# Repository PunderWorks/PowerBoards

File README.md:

# Power Boards

Small PCBs for power regulation and distribution.

Each board's electrical design is written in [Stackup](https://github.com/stackup-eda/stackup) KDL, which
is the source of truth for the circuit; there are no KiCad schematics. The layout is done in KiCad
(currently 10), linked to the KDL through a `.stackup_sch` file and synced with the Stackup KiCad plugin.

## Boards

<p align="center">

</p>

| Board | Folder | Purpose | Status |
|---|---|---|---|
| Regulator | [`PCB/regulator/`](PCB/regulator) | A plug-in Pololu D42V55Fx regulator (any output version: 5 V, 12 V, ...) feeding four WAGO 2601 outputs over V+ and GND planes. 9-32 V in, 6 A out (5 A with the 12 V module) | Design done, first-pass layout |
| Distribution | [`PCB/distribution/`](PCB/distribution) | Six interchangeable power terminals in a 3 x 2 grid (any one can be the input) over shared V+ and GND planes, WAGO 2601 lever terminals. 17.5 A total | Initial layout done |
| Distribution, inline | [`PCB/distribution-inline/`](PCB/distribution-inline) | The distribution board with five terminals in a single row (65.5 x 24 mm). 17.5 A total | Initial layout done |

Each board's README has its ratings, a parts list with Mouser, DigiKey and LCSC numbers, assembly
steps and the design decisions behind it. The purchasing BOM for each is in
`PCB/<board>/production/bom/`.

## Repository layout

| Path | Contents |
|---|---|
| [`manifest.kdl`](manifest.kdl) | Stackup version and the parts library, pinned by commit. Shared by every board |
| `PCB/<board>/` | One folder per board: its KiCad project (`<board>.kicad_pro`, `.kicad_pcb`, `.stackup_sch`) and the folders below |
| `PCB/<board>/stackup/` | `board.kdl`, the board's circuit |
| [`PCB/libraries/stackup/`](PCB/libraries/stackup) | `parts.kdl`, the Stackup parts shared by every board |
| `PCB/<board>/diagrams/` | Layout floorplans for circuits with real layout stakes (switching loops, thermal pads, high-current paths) |
| `PCB/<board>/analysis/` | Generated analysis output. Only `manifest.json` is committed |
| `PCB/<board>/assets/` | Board renders used in the READMEs |
| `PCB/<board>/production/` | Fab outputs: `bom/` (the purchasing BOM), `gerbers/`, `jlcpcb/`, `placement/` |
| [`PCB/libraries/`](PCB/libraries) | KiCad footprints (`PowerBoards.pretty`) and 3D models shared by all boards |
| [`PCB/datasheets/`](PCB/datasheets) | Manufacturer datasheets for the parts used, shared by all boards |
| [`scripts/export_production.sh`](scripts/export_production.sh) | Regenerates every board's `production/` files |
| [`scripts/spice/`](scripts/spice) | ngspice simulations of the power, enable and protection circuits |
| [`graphics/`](graphics) | Logos and images |

To add a board, create `PCB/<board>/` with the same subfolders as an existing one and add it to the
table above.

## Working on a board

Run these from the repository root.

```bash
# Check the circuit
stackup check PCB/<board>/stackup/board.kdl

# Export the purchasing BOM
stackup bom PCB/<board>/stackup/board.kdl --locked -o <board>-bom.csv

# Regenerate the fab files (BOM, Gerbers, drills, placement, upload zip) for one board or all of them
scripts/export_production.sh [<board>]
```

After `stackup check` passes, open `PCB/<board>/<board>.kicad_pcb` in KiCad and sync it with the Stackup
plugin.

## Contributing

All changes go through pull requests; nothing is pushed directly to `main`. History is kept linear, so
PRs land by rebase.

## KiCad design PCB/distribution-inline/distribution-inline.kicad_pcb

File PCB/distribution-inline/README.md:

# Inline Distribution Board

Five identical 2-pole terminals in a single row share a V+ plane (`VPWR`, top copper) and a ground
plane (`GND`, bottom copper). Any terminal can be the input; the other four are outputs. There are no
active or passive components.

This is the [distribution board](../distribution/README.md) laid out in one row instead of a 3 x 2 grid,
for where a long, narrow board fits better. The terminal, ratings and design decisions are the same;
only the layout differs, and that is described here.

## Features

- **One in, four out, any way round.** Every terminal is the same, so any one can be the input.
- **17.5 A total** through solid copper planes on both layers, with 16 AWG wire.
- **Tool-free wiring.** WAGO 2601 lever terminals take 26-16 AWG wire; strip 8-9 mm and push it in.
- **Long and narrow.** 65.5 x 24 mm, with every wire leaving from the same edge.
- **Safe to mount with metal hardware.** Four M3 holes with copper kept clear of each.
- **Five parts, all through-hole.**

## Ratings

| | |
|---|---|
| Current | **17.5 A total** through whichever terminal is the input, with 16 AWG wire (IEC/EN 60664-1 rating of the terminals). **10 A** if you need the UL/CSA rating. |
| Wire | 26-16 AWG solid, 24-16 AWG fine-stranded. Strip 8-9 mm. |
| Voltage | DC power distribution, far below the terminals' 160 V IEC / 300 V UL rating. |
| Polarity | `+` and `-` are printed behind every terminal. Any terminal can be the input. |
| Mounting | Four M3 holes. Screws and standoffs may be metal: copper is kept clear of every hole. |

The input terminal carries the sum of every output's current, so the 17.5 A limit applies to the total,
not to each output. See the [distribution board README](../distribution/README.md#terminal-wago-2601-1102)
for the terminal's datasheet figures.

The electrical design is in [Stackup KDL](stackup/board.kdl), using the shared
[parts file](../libraries/stackup/parts.kdl). The KiCad PCB (`distribution-inline.kicad_pcb`) is linked
to it through `distribution-inline.stackup_sch`; sync it with the Stackup KiCad plugin. Run
`stackup check PCB/distribution-inline/stackup/board.kdl --locked` from the repository root before
syncing.

## What to buy

The purchasing BOM is [`production/bom/distribution-inline-bom.csv`](production/bom/distribution-inline-bom.csv), exported from
the Stackup design (`stackup bom PCB/distribution-inline/stackup/board.kdl --locked`).

| Qty | Ref | Part | Manufacturer / MPN | Mouser | DigiKey | LCSC |
|---|---|---|---|---|---|---|
| 5 | J1-J5 | Lever terminal, 2-pole, 3.5 mm, horizontal entry | WAGO 2601-1102 | 1089-2601-1102 | 2946-2601-1102-ND | C7509568 |
| 4 | — | M3 screws and standoffs to mount the board (not on the BOM) | Any; metal is fine, copper is kept clear of the holes | | | |

The 2601-3102 is the vertical, top-entry version of the same block; it is not a substitute.

## Ordering

Fab files are in [`production/`](production/), regenerated with `scripts/export_production.sh distribution-inline`
from the repository root:

| File | Contents |
|---|---|
| [`production/jlcpcb/distribution-inline-gerbers.zip`](production/jlcpcb/distribution-inline-gerbers.zip) | Everything a fab needs to make the bare board: upload this |
| [`production/gerbers/`](production/gerbers/) | The same files unzipped: Gerbers (X2, Protel extensions), PTH and NPTH Excellon drills, drill maps, job file |
| [`production/bom/distribution-inline-bom.csv`](production/bom/distribution-inline-bom.csv) | Purchasing BOM with Mouser, DigiKey and LCSC numbers |
| [`production/placement/distribution-inline-pos.csv`](production/placement/distribution-inline-pos.csv) | Placement file (mm), for an assembler |

Board options: **65.5 x 24 mm, 2 layers, 1.6 mm FR-4, 1 oz copper, blue solder mask, white silkscreen**,
any surface finish (HASL lead-free is fine). Every feature is far above standard fab minimums. The five terminals are through-hole and quick to hand-solder; JLCPCB can also assemble them (LCSC C7509568).

## Assembly

1. Fit the 5 terminals with their wire entries at the board edge and solder both pins of each pole.
   The pins carry the full current, so make them full, shiny fillets.
2. Check continuity between all 5 `+` pins and between all 5 `-` pins, and that `+` and `-` are
   not shorted.
3. Wire the supply to any one terminal and the loads to the others, keeping the total within the rating.

## Hardware overview

| Ref | Function | Part |
|---|---|---|
| J1-J5 | Power terminal, input or output | WAGO 2601-1102 |

Every terminal has pin 1 (square pad, `+` on the silkscreen) on `VPWR` and pin 2 (`-`) on `GND`.

## Layout

- **65.5 x 24 mm, one row.** J1-J5 sit on the same 10 mm pitch as the 3 x 2 board (8.5 mm body plus
  room to work the levers), all with their wires entering from the bottom edge. The wire entry faces
  are flush with that edge, so the 10 `silk_edge_clearance` DRC warnings (two per terminal) are
  expected, as on the 3 x 2 board.
- **Ratings across the top.** A single row leaves no side strips tall enough for text, so "17.5A MAX
  TOTAL / 16 AWG" and "WIRE 26-16 AWG / STRIP 8-9mm" run as two lines along the top edge, above the `+`
  and `-` marks.
- **Four M3 mounting holes on side extensions**, two each side, each centre 4.45 mm from the nearest
  terminal body, with the same 8 mm copper keep-out on both layers.
- **Planes, not traces.** V+ on top and GND on the bottom span the whole board, joined to the pads
  through thermal reliefs with 1.0 mm spokes (8 mm of copper per pole), as on the 3 x 2 board.
- **Back:** the 10 mm PunderWorks logo beside "POWER DISTRIBUTION" and the IEC/UL ratings.

## Bench checklist

- Before connecting a load, check continuity between all five `+` pins and between all five `-` pins,
  and confirm there is no short between V+ and GND.
- Run the full intended load through the input and one output, and check the input terminal and the
  board near it for heating.

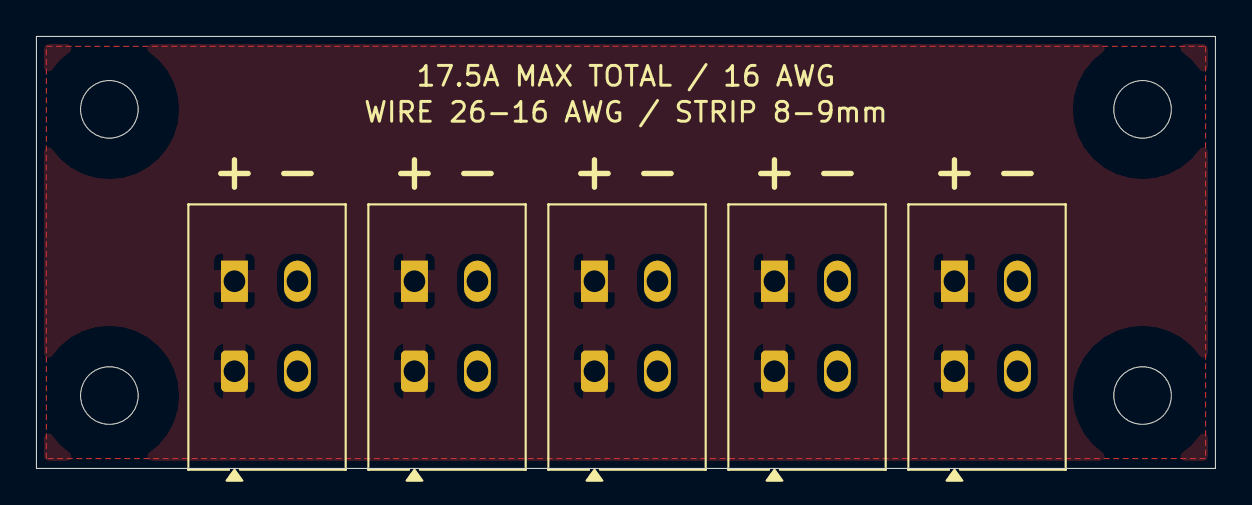
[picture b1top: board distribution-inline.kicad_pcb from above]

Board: 2 copper layers, 65.5 x 24.0 mm, 10 parts (1 on the bottom side), 2 nets, no tracks yet.

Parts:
H1, H2, H3, H4: MountingHole_3.2mm_M3
J1, J2, J3, J4, J5: WAGO 2601-1102; WAGO_2601-1102_Horizontal
LOGO1: PunderWorks_Logo_10mm

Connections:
GND: J1.2, J2.2, J3.2, J4.2, J5.2
VPWR: J1.1, J2.1, J3.1, J4.1, J5.1

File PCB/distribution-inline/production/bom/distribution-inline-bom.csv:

Refs,Quantity,Value,Footprint,MF,MPN,LCSC,Mouser,DigiKey,Hand,DNP
"J1,J2,J3,J4,J5","5","WAGO 2601-1102","PowerBoards:WAGO_2601-1102_Horizontal","WAGO","2601-1102","C7509568","1089-2601-1102","2946-2601-1102-ND","",""

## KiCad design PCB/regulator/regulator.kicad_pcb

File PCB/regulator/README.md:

# Regulator Board

A power distribution board with a plug-in step-down regulator. One WAGO terminal takes the battery and
feeds a Pololu D42V55Fx module plugged into a socket in the middle of the board; the module's output
feeds a V+ plane shared by four more WAGO terminals, over a GND plane. The output voltage is whichever
module is plugged in: **D42V55F5 for 5 V, D42V55F12 for 12 V**, or any other D42V55Fx version.
Swapping the module changes the board's output; nothing else on the board changes.

## Features

- **Battery in, regulated power out to four terminals.** 9-32 V in (24 V batteries up to 32 V
  peak, or 12 V systems with the 5 V module), up to 6 A out in total.
- **Plug-in regulator.** The Pololu module sits in a socket on its own headers, so one board covers
  every output voltage, and a module can be swapped without desoldering anything.
- **Tool-free wiring.** WAGO 2601 lever terminals take 26-16 AWG wire; strip 8-9 mm and push it in.
- **Protected input.** The module has reverse-polarity, over-current and over-temperature
  protection. An input capacitor on the board damps the voltage spike when a charged battery is
  plugged in (simulated: 42 V worst case instead of 57 V, against the module's 60 V limit).
- **Label it.** A blank `VOUT` box on the silkscreen for the voltage of the module fitted, `+`/`-`
  behind every terminal, and the ratings printed on both sides.
- **All through-hole.** Seven parts plus the module, easy to hand-solder.

## Ratings

| | 5 V (D42V55F5) | 12 V (D42V55F12) |
|---|---|---|
| Input | 9-32 V DC (module: up to 60 V) | 14-32 V DC (module: up to 60 V) |
| Output current, total | **6 A** | **5 A** |
| What limits it | The module's two VOUT header pins, 3 A each | The module's thermal limit, derated for an enclosure |
| Module alone, 24-32 V in, open air | 7.1-6.8 A | 5.9-5.4 A |
| Wire | 26-16 AWG, strip 8-9 mm (WAGO 2601) | Same |

Other D42V55Fx output versions fit the same socket; the board limit is still 6 A, and the module's own
limit comes from Pololu's graph. The four outputs share the total; it is not per output. Input current
is far lower than the output current: about 2.8 A at 24 V in for 12 V x 5 A out. The terminals
(17.5 A IEC) are nowhere near their limit.

Module currents are from Pololu's "maximum continuous output current" graph on the
[product page](../datasheets/Pololu_D42V55F5.html) (room temperature, still air, no heat sinking).
The 9 V and 14 V input minimums are a working allowance for dropout at full load, not Pololu figures;
see the dropout graph on the product page.

## What to buy

### Board parts

The purchasing BOM is [`production/bom/regulator-bom.csv`](production/bom/regulator-bom.csv),
exported from the Stackup design (`stackup bom PCB/regulator/stackup/board.kdl --locked`).

| Qty | Ref | Part | Manufacturer / MPN | Mouser | DigiKey | LCSC |
|---|---|---|---|---|---|---|
| 5 | J1-J5 | Lever terminal, 2-pole, 3.5 mm, horizontal entry | WAGO 2601-1102 | 1089-2601-1102 | 2946-2601-1102-ND | C7509568 |
| 1 | J6 | Module socket: female header 2x6, 2.54 mm, through-hole | Samtec SSW-106-01-T-D | 200-SSW10601TD | 612-SSW-106-01-T-D-ND | C3323806 |
| 1 | C1 | Electrolytic capacitor, 100 µF 63 V, radial 8 x 11.5 mm, 3.5 mm lead spacing | Rubycon 63ZLJ100M8X11.5 | 232-63ZLJ100M8X11.5 | 1189-63ZLJ100M8X11.5-ND | C694359 |

Substitutes: Sullins PPTC062LFBN-RC for J6. For C1, any low-impedance 100 µF 63 V (or higher)
105 °C electrolytic that is 8 mm in diameter with 3.5 mm lead spacing; a 10 mm can has 5 mm spacing
and won't fit the footprint.

### Not on the board

| Qty | Item | Notes |
|---|---|---|
| 1 | Pololu D42V55Fx regulator | [pololu.com/category/354](https://www.pololu.com/category/354). D42V55F5 (#5571) for 5 V, D42V55F12 (#5577) for 12 V, or another version. Comes with the male headers it plugs in on |
| 3 | Round nylon spacer, #2/M2, 3/16" (4.76 mm) OD x 7/16" (11.13 mm), unthreaded: **Bivar 9913-437** | Mouser 749-9913-437, DigiKey 492-1047-ND. Optional but recommended in a moving droid: holds the module down |
| 3 | Nylon pan head screw, M2 x 16 mm, Phillips: **Essentra 50M020040P016** | DigiKey 145-50M020040P016-ND (Mouser 144-50M020040P016). Goes down through the module, the spacer and the board. M2 x 20 (50M020040P020) also works, with more thread below the nut |
| 3 | Nylon hex nut, M2: **Essentra 04M020040HN** | Mouser 144-04M020040HN, DigiKey RPC7084-ND. Under the board |
| 4 | M3 screws and standoffs | To mount the board. Metal is fine: copper is kept clear of the holes |

## Ordering

Fab files are in [`production/`](production/), regenerated with `scripts/export_production.sh regulator`
from the repository root:

| File | Contents |
|---|---|
| [`production/jlcpcb/regulator-gerbers.zip`](production/jlcpcb/regulator-gerbers.zip) | Everything a fab needs to make the bare board: upload this |
| [`production/gerbers/`](production/gerbers/) | The same files unzipped: Gerbers (X2, Protel extensions), PTH and NPTH Excellon drills, drill maps, job file |
| [`production/bom/regulator-bom.csv`](production/bom/regulator-bom.csv) | Purchasing BOM with Mouser, DigiKey and LCSC numbers |
| [`production/placement/regulator-pos.csv`](production/placement/regulator-pos.csv) | Placement file (mm), for an assembler |

Board options: **55.5 x 46 mm, 2 layers, 1.6 mm FR-4, 1 oz copper, blue solder mask, white silkscreen**,
any surface finish (HASL lead-free is fine). Every feature is far above standard fab minimums. All seven parts are through-hole; JLCPCB can assemble them (it has LCSC numbers for all three line items), but they are quick to hand-solder. The Pololu module and the spacer hardware are bought separately (see What to buy).

## Assembly

1. Solder C1 with its `+` lead in the pad nearest the socket (the stripe on the can is `-`), then J6
   and the five WAGO terminals. Keep the socket square to the board so the module sits level.
2. Solder the module's supplied male headers to the module (long pins down), using the socket as a
   jig: plug the headers into J6, sit the module on them, and solder from the top.
3. Before plugging the module in, check there is no short from VIN, VRP or VOUT to GND, and power
   the board from a current-limited supply to check J1 reaches J6.
4. Stand a spacer over each of the three M2 holes (H5-H7), then plug the module in on top, with its
   body over the outline on the silkscreen and its holes over the spacers. Push an M2 x 16 nylon
   screw down through each module hole, spacer and board, and fit a nylon nut underneath. Snug the
   nuts by hand; don't pull the module down harder than the socket seats it. Write the output voltage in the `VOUT` box.
5. Wire the battery to J1 (`IN`) and the loads to J2-J5. The bench checklist below has the first
   power-up checks.

The electrical design is in [Stackup KDL](stackup/board.kdl), using the shared
[parts file](../libraries/stackup/parts.kdl). The KiCad PCB (`regulator.kicad_pcb`) is linked to it
through `regulator.stackup_sch`; sync it with the Stackup KiCad plugin. Run
`stackup check PCB/regulator/stackup/board.kdl --locked` from the repository root before syncing.

## Design decisions

- **A plug-in module, not a regulator on the board.** The board stays passive and through-hole, and one
  PCB covers every output voltage. The D42V55Fx family was chosen over the D36V50Fx for its 60 V input
  (against 50 V), which leaves room above 32 V battery peaks and hot-plug spikes, and for holding more
  current near 32 V in. Its pins are a 2x6 grid on 0.1" pitch in the order EN/PG, VRP, VIN, GND, GND,
  VOUT, with EN on the edge row and PG on the inner row. The dimension drawing puts the edge row 1.27 mm
  and the inner row 3.81 mm from the module edge, with the six positions centered (6.35 mm from each
  end). The D36V50Fx has the same pin order and should fit the same socket, but that is from Pololu's
  pinout photos; its standoff holes have not been checked against these.
- **One input capacitor, no TVS.** With the module alone, simulated hot-plug at 32 V through 0.5-2 µH
  of battery lead peaks at up to 57 V at VIN, close to the 60 V limit. C_IN brings the worst case to 42 V.
  See `scripts/spice/regulator_hotplug_sim.py` (`--bare` for the module alone).
- **C_IN is on VRP, not VIN.** VRP is the module's input after its reverse-voltage protection. A
  polarized capacitor there is never reverse-biased by a battery wired backwards, so there is no need for
  a bipolar capacitor (the 63 V ones are poorly stocked) or a back-to-back pair. The simulation models
  the unpublished protection both as a closed switch and as a bare diode; both pass.
- **No extra output capacitor.** The module carries its own output capacitors, and Pololu gives no
  guidance on adding more.
- **EN and PG unconnected.** The module pulls EN up to VIN through 1 MΩ, so it is always on. No on/off
  switch, LED, servo headers, USB or VIN passthrough: the board is meant to stay simple. A distribution
  board on the battery side gives a passthrough if one is needed.
- **Inspiration:** the Sure Robotics DC Converter (6 A, 9-36 V in, 5/6 V out, four screw-terminal
  outputs).

## Layout

55.5 x 46 mm, two layers, 1 oz copper. Top copper is a VOUT pour, bottom copper a GND pour, both over
the whole board, joined to pads through thermal reliefs with 1.0 mm spokes (as on the distribution
board). VIN runs as a 2.5 mm top trace from J1 to the socket (1.5 mm along the socket row, between the
VRP and GND pins); VRP is a 1.0 mm trace from the socket to C1.

- **J1 (input) alone on the top edge, J2-J5 (outputs) on the bottom edge,** wires entering from the
  edge, on the distribution board's 10 mm pitch. Keeping the input on its own edge makes it hard to
  wire a battery into an output. `+`/`-` sit behind every terminal body.
- **Module in the middle, socket on its left edge.** The socket is rotated so EN/PG is at the bottom and
  VOUT at the top, which puts VIN facing J1 and VRP beside C1. The module body (25.4 mm square, outlined
  on the silkscreen with its pin names inside) extends right of the socket, over nothing but the planes.
- **C1 right beside the VRP pins,** clear of the module outline (it is 11.5 mm tall).
- **M2 holes for holding the module down (H5-H7)**, at the positions in Pololu's
  [dimension drawing](../datasheets/POLOLU_D42V55Fx_dimensions.pdf): Ø2.2 mm, 2.2 mm in from the
  module's edges and 21.1 mm apart. Two are at the ends of the pin edge, one at the far corner on the
  EN/PG side. Each has a 5.5 mm copper keep-out on both layers. The socket (8.51 mm tall, Samtec
  drawing) plus the module's 2.54 mm header plastic puts the module's PCB 11.05 mm above this one, so
  the module is held by a 7/16" (11.13 mm) round nylon spacer (Bivar 9913-437) on an M2 x 16 nylon
  screw and nut. All-nylon hardware can't short anything. There is no stocked nylon M2 x 11 mm
  female-female hex standoff, and a round spacer has no corners to orient: H5 sits 2.2 mm from the pin
  edge, and the 4.76 mm spacer there clears the socket body (15.75 mm long, Samtec drawing) by
  0.24 mm. The holes' courtyards are the spacer (2.4 mm radius), which reaches into the socket
  courtyard's 0.5 mm margin at H5; a custom DRC rule in `regulator.kicad_dru` allows exactly that pair,
  with the reason.
- **Four M3 corner holes** with 8 mm copper keep-outs on both layers, so metal screws and standoffs are
  safe, as on the distribution board.
- **Silkscreen:** input range and wire size on the left strip. On the right strip, "OUT: 6A MAX TOTAL"
  and a blank box labelled `VOUT` for the builder to write in the output voltage of the module fitted;
  the board isn't tied to 5 V or 12 V, so it names no versions. "ANY OUTPUT VERSION" and the pin names
  sit inside the module outline. The back has the title and "D42V55Fx 6A MAX TOTAL". 6 A is the board's
  limit (the module's two VOUT pins); a module may be lower, as the 12 V one is (see Ratings).
- **QR code** on the back, linking to the repository (`HTTPS://GITHUB.COM/PUNDERWORKS/POWERBOARDS`) for
  the assembly notes and BOM. It is a KiCad barcode object like the PowerSense board's: QR, ECC level L,
  upper case so it encodes in the compact alphanumeric mode, 9.5 mm square (0.38 mm modules) to keep
  KiCad's 1 mm barcode clearance from C1 and J2. GitHub folder paths are case-sensitive, so it points at
  the repository rather than this folder.
- **Logo:** the PunderWorks logo (`PowerBoards:PunderWorks_Logo_14mm`, 14 x 10.3 mm) on the back,
  behind the module, as on the PowerSense and Snips boards. It is a board-only silkscreen footprint
  (no pads, excluded from the BOM and placement files) generated by `scripts/make_logo_footprint.py`
  from [`PCB/libraries/logos/PunderWorks-black.png`](../libraries/logos/PunderWorks-black.png).
  Another size: `python3 scripts/make_logo_footprint.py PCB/libraries/logos/PunderWorks-black.png
  <width_mm> PCB/libraries/PowerBoards.pretty/PunderWorks_Logo_<width>mm.kicad_mod`.
- **DRC:** 10 `silk_edge_clearance` warnings, for the same reason as on the distribution board: the
  WAGO footprints' silkscreen crosses the board edge because the wire entry faces are flush with it.
  Nothing else.

## Not yet verified

- The D42V55Fx's reverse-voltage limit is not published. Pololu says only that VIN has reverse
  protection.
- The module's input capacitance and protection circuit are not published. The simulation sweeps both.
- Whether a D36V50Fx fits (pin order from photos only; its mounting holes not checked).

## Bench checklist

- Before fitting the module, check continuity: J1 pin 1 to J6 pads 5-6; J2-J5 pin 1 to J6 pads 11-12;
  every terminal's pin 2 to J6 pads 7-10; C1 `+` to J6 pads 3-4. Confirm there is no short from VIN,
  VRP or VOUT to GND.
- Check that a D42V55F5 and a D42V55F12 both seat fully in J6, with the body over the marked outline. If
  a D36V50Fx is available, check that it seats too. Check that the module's holes line up with H5-H7,
  and that the 11.13 mm spacers sit between the boards without lifting the module out of the socket.
- Power up from a current-limited bench supply at 12 V and then 32 V, with no load. Check VOUT.
- Hot-plug a charged battery (or a 32 V supply on a long lead) several times, scoping VIN at J6.
  Expect under about 45 V peak.
- Run the rated load (6 A at 5 V, 5 A at 12 V) through all four outputs for 15 minutes at the highest
  battery voltage. Check the module, C1 and the terminals for heat, and VOUT for droop.

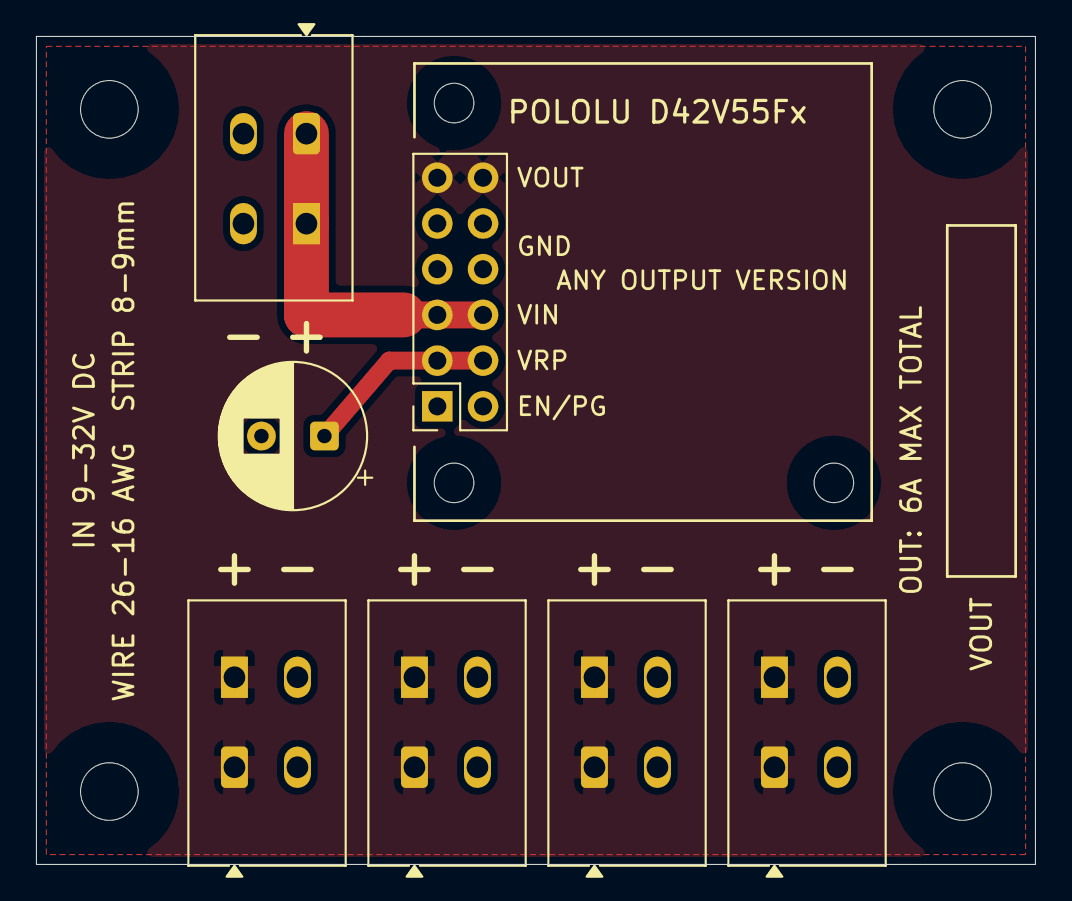
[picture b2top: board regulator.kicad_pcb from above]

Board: 2 copper layers, 55.5 x 46.0 mm, 15 parts (1 on the bottom side), 4 nets.

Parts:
C1: 100µF 63V radial 8x11.5mm; CP_Radial_D8.0mm_P3.50mm
H1, H2, H3, H4: MountingHole_3.2mm_M3
H5, H6, H7: MountingHole_2.2mm_M2
J1, J2, J3, J4, J5: WAGO 2601-1102; WAGO_2601-1102_Horizontal
J6: Pololu D42V55Fx socket; PinSocket_2x06_P2.54mm_Vertical
LOGO1: PunderWorks_Logo_14mm

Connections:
GND: C1.2, J1.2, J2.2, J3.2, J4.2, J5.2, J6.7, J6.8, J6.9, J6.10
VIN: J1.1, J6.5, J6.6
VOUT: J2.1, J3.1, J4.1, J5.1, J6.11, J6.12
VRP: C1.1, J6.3, J6.4
